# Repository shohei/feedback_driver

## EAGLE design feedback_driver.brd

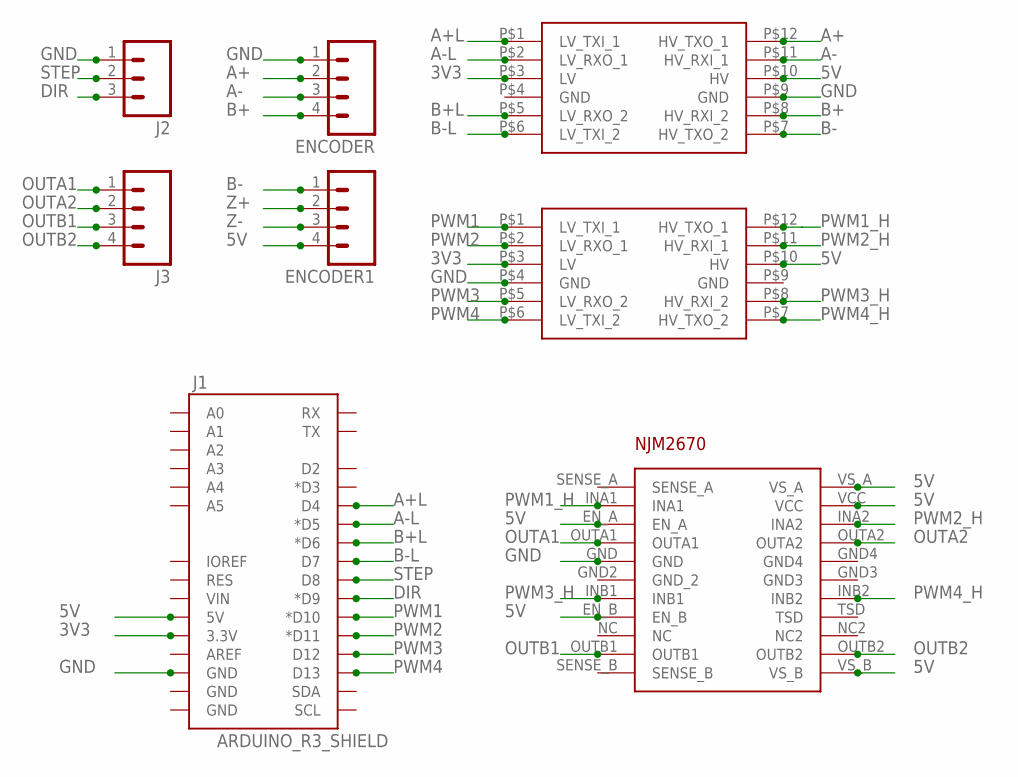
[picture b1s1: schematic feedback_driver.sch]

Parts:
ENCODER, ENCODER1: M04LONGPADS; 1X04_LONGPADS
J1: ARDUINO_R3_SHIELD; UNO_R3_SHIELD
J2: M03LONGPADS; 1X03_LONGPADS
J3: M04LONGPADS; 1X04_LONGPADS
U$1, U$2: LOGIC_LEVEL_CONVERTER
U$3: NJM2670

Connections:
3V3: J1.3.3V, U$1.P$3 (LV), U$2.P$3 (LV)
5V: ENCODER1.4, J1.5V, U$1.P$10 (HV), U$2.P$10 (HV), U$3.EN_A, U$3.EN_B, U$3.VCC, U$3.VS_A, U$3.VS_B
A+: ENCODER.2, U$1.P$12 (HV_TXO_1)
A+L: J1.D4, U$1.P$1 (LV_TXI_1)
A-: ENCODER.3, U$1.P$11 (HV_RXI_1)
A-L: J1.D5 (*D5), U$1.P$2 (LV_RXO_1)
B+: ENCODER.4, U$1.P$8 (HV_RXI_2)
B+L: J1.D6 (*D6), U$1.P$5 (LV_RXO_2)
B-: ENCODER1.1, U$1.P$7 (HV_TXO_2)
B-L: J1.D7, U$1.P$6 (LV_TXI_2)
DIR: J1.D9 (*D9), J2.3
GND: ENCODER.1, J1.GND@2 (GND), J2.1, U$1.P$9 (GND), U$2.P$4 (GND), U$3.GND
OUTA1: J3.1, U$3.OUTA1
OUTA2: J3.2, U$3.OUTA2
OUTB1: J3.3, U$3.OUTB1
OUTB2: J3.4, U$3.OUTB2
PWM1: J1.D10 (*D10), U$2.P$1 (LV_TXI_1)
PWM1_H: U$2.P$12 (HV_TXO_1), U$3.INA1
PWM2: J1.D11 (*D11), U$2.P$2 (LV_RXO_1)
PWM2_H: U$2.P$11 (HV_RXI_1), U$3.INA2
PWM3: J1.D12, U$2.P$5 (LV_RXO_2)
PWM3_H: U$2.P$8 (HV_RXI_2), U$3.INB1
PWM4: J1.D13, U$2.P$6 (LV_TXI_2)
PWM4_H: U$2.P$7 (HV_TXO_2), U$3.INB2
STEP: J1.D8, J2.2
Z+: ENCODER1.2
Z-: ENCODER1.3

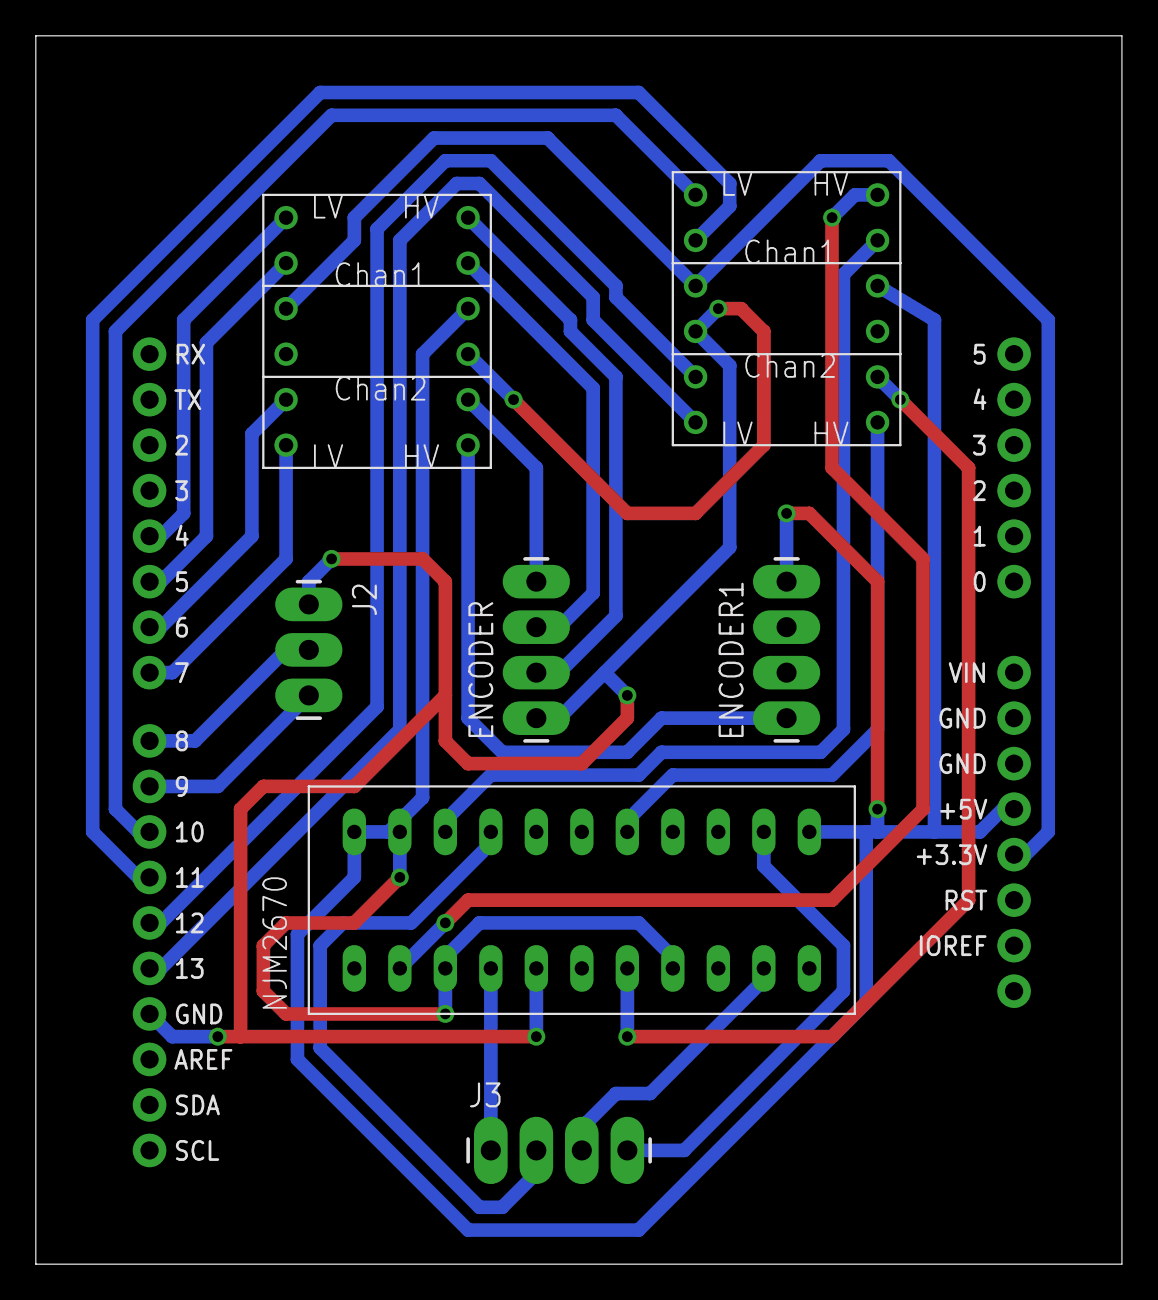
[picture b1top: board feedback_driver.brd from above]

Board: 2 copper layers, 60.6 x 68.6 mm, 8 parts (0 on the bottom side), 25 nets.

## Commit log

2016-11-22 add readme
2016-11-25 update to ver2
2016-11-25 add image
2016-11-25 update image
2016-12-02 add implementation

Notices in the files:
parts and their libraries:
SparkFun-Connectors: Licensing: Creative Commons ShareAlike 4.0 International - https://creativecommons.org/licenses/by-sa/4.0
